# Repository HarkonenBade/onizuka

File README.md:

# onizuka
An FTDI based programming master board. With various daughter boards for programming specific modules.

## Current Daughter Boards
* ESP8266 (ESP-01, ESP-02, ESP-12E)

## License
Onizuka is licensed under [Creative Commons Attribution-ShareAlike 4.0 International (CC BY-SA 4.0)](http://creativecommons.org/licenses/by-sa/4.0/).

Psyduck (used in image on the ESP8266 board, due to the pun on ESP->ESP->Psychic) is Trademark & © of Nintendo 1996-2015

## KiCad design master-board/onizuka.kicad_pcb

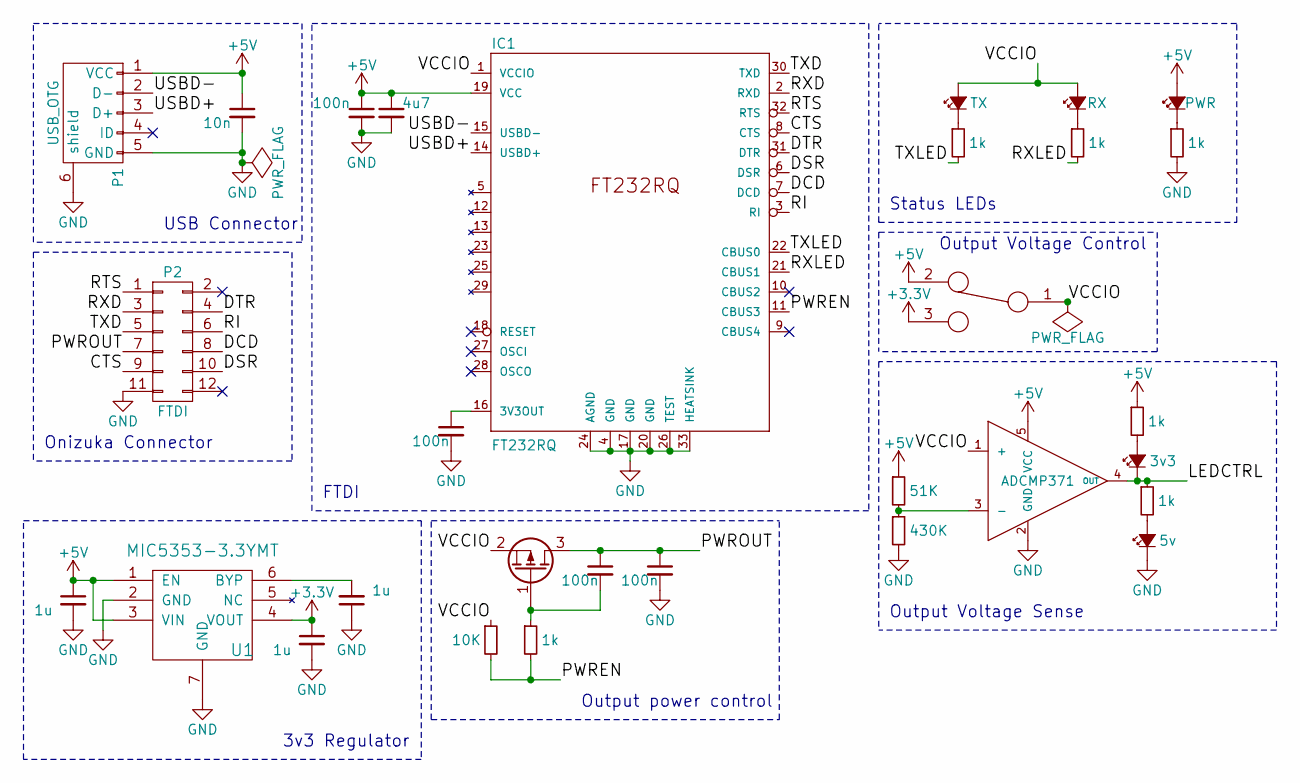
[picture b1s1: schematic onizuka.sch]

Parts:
C1, C4, C5, C6: 100n; C_0402; Farnell 2524677
C2: 10n; C_0402; Farnell 2524674
C3: 4u7; C_0402; Farnell 2426952
C7, C8, C9: 1u; C_0402; Farnell 2496813
D1: TX; LED_0603; Farnell 2290329
D2: RX; LED_0603; Farnell 8554609
D3: PWR; LED_0603; Farnell 8554609
D4: 3v3; LED_0603; Farnell 2290330
D5: 5v; LED_0603; Farnell 2290329
IC1: FT232RQ; FTDI-FT232RQ-QFN-32; Farnell 1146033
IC2: ADCMP371; SC-70-5; Farnell 2376801
P1: USB_OTG; USB_Micro-B; Farnell 2506104
P2: FTDI; Socket_Strip_Angled_2x06; Farnell 1668355
Q1: Q_PMOS_GSD; SOT-23; Farnell 1894738
R1, R2, R3, R4, R7, R8: 1k; R_0402; Farnell 1358043
R5: 51K; R_0402; Farnell 1358088
R6: 430K; R_0402; Farnell 1358113
R9: 10K; R_0402; Farnell 1358069
SW1: SPDT; 450301014042; Farnell 2134452
U1: MIC5353-3.3YMT; Thin_MLF_6_1.6mm_0.5mm_pitch; Farnell 2510347

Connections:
+3V3: C8.1, SW1.3, U1.4 (VOUT)
+5V: C2.1, C3.1, C4.1, C7.1, D3.2 (A), IC1.19 (VCC), IC2.5 (VCC), P1.1 (VCC), R5.1, R7.1, SW1.2, U1.1 (EN), U1.3 (VIN)
/CTS: IC1.8 (CTS), P2.9
/DCD: IC1.7 (DCD), P2.8
/DSR: IC1.6 (DSR), P2.10
/DTR: IC1.31 (DTR), P2.4
/LEDCTRL: D4.1 (K), IC2.4 (OUT), R8.1
/PWREN: IC1.11 (CBUS3), R4.2, R9.2
/PWROUT: C5.1, C6.1, P2.7, Q1.3 (D)
/RI: IC1.3 (RI), P2.6
/RTS: IC1.32 (RTS), P2.1
/RXD: IC1.2 (RXD), P2.3
/RXLED: IC1.21 (CBUS1), R2.2
/TXD: IC1.30 (TXD), P2.5
/TXLED: IC1.22 (CBUS0), R1.2
/USBD+: IC1.14 (USBD+), P1.3 (D+)
/USBD-: IC1.15 (USBD-), P1.2 (D-)
/VCCIO: D1.2 (A), D2.2 (A), IC1.1 (VCCIO), IC2.1 (+), Q1.2 (S), R9.1, SW1.1
GND: C1.2, C2.2, C3.2, C4.2, C6.2, C7.2, C8.2, C9.1, D5.1 (K), IC1.4 (GND), IC1.17 (GND), IC1.20 (GND), IC1.24 (AGND), IC1.26 (TEST), IC1.33 (HEATSINK), IC2.2 (GND), P1.5 (GND), P1.6 (shield), P2.11, R3.2, R6.2, U1.2 (GND), U1.7 (GND)
unnamed: C1.1, IC1.16 (3V3OUT)
unnamed: C5.2, Q1.1 (G), R4.1
unnamed: C9.2, U1.6 (BYP)
unnamed: D1.1 (K), R1.1
unnamed: D2.1 (K), R2.1
unnamed: D3.1 (K), R3.1
unnamed: D4.2 (A), R7.2
unnamed: D5.2 (A), R8.2
unnamed: IC2.3 (-), R5.2, R6.1

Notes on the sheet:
USB Connector
FTDI
3v3 Regulator
Output power control
Output Voltage Control
Onizuka Connector
Status LEDs
Output Voltage Sense

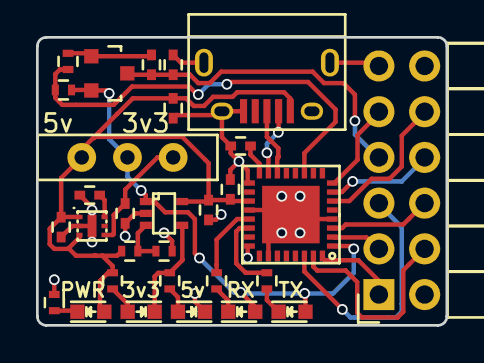
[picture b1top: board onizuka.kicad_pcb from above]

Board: 2 copper layers, 22.8 x 16.0 mm, 30 parts (0 on the bottom side), 28 nets.

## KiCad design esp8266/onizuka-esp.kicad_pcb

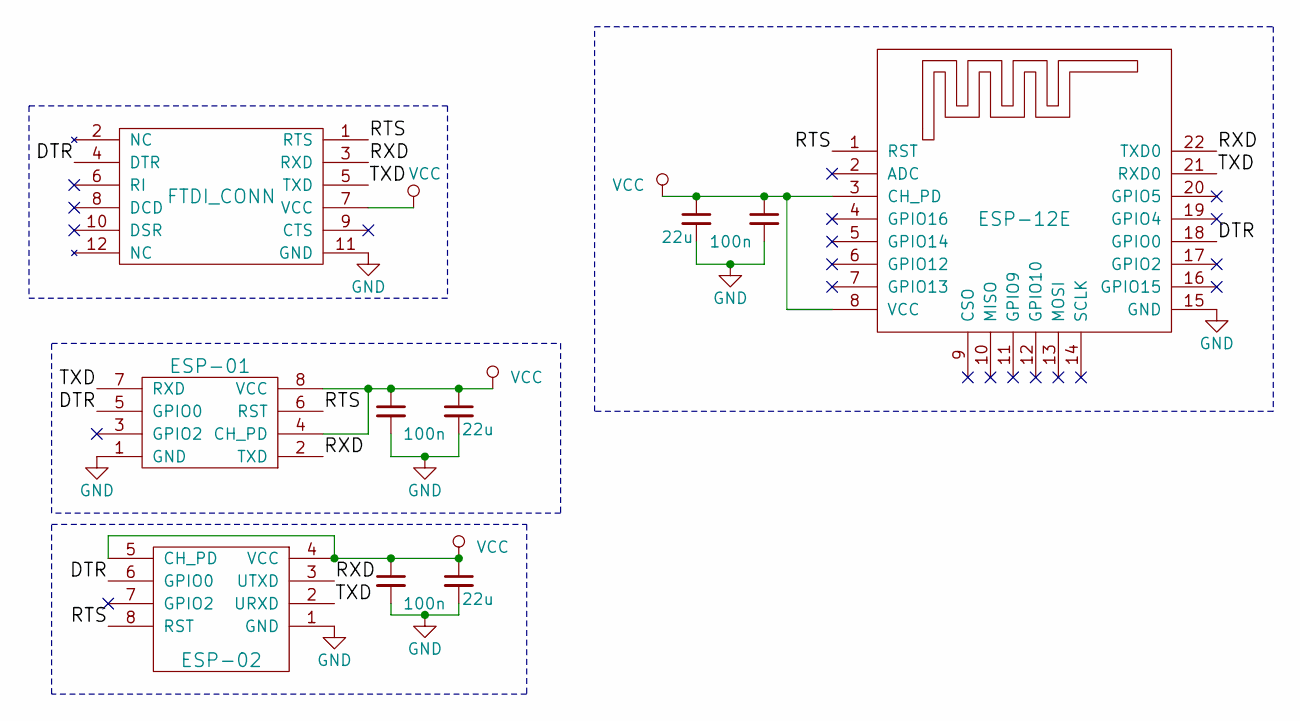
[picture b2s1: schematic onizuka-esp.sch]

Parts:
C1, C4, C6: 100n; C_0603; Farnell 2524817
C2, C3, C7: 22u; C_0603; Farnell 2494232
P1: FTDI_CONN; Pin_Header_Angled_2x06; Farnell 1593452
U1: ESP-01; Farnell 1593489
U2: ESP-12E; ESP-12E-Program
U3: ESP-02; ESP-02-Program

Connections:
/DTR: P1.4 (DTR), U1.5 (GPIO0), U2.18 (GPIO0), U3.6 (GPIO0)
/RTS: P1.1 (RTS), U1.6 (RST), U2.1 (RST), U3.8 (RST)
/RXD: P1.3 (RXD), U1.2 (TXD), U2.22 (TXD0), U3.3 (UTXD)
/TXD: P1.5 (TXD), U1.7 (RXD), U2.21 (RXD0), U3.2 (URXD)
GND: C1.2, C2.2, C3.2, C4.2, C6.2, C7.2, P1.11 (GND), U1.1 (GND), U2.15 (GND), U3.1 (GND)
VCC: C1.1, C2.1, C3.1, C4.1, C6.1, C7.1, P1.7 (VCC), U1.4 (CH_PD), U1.8 (VCC), U2.3 (CH_PD), U2.8 (VCC), U3.4 (VCC), U3.5 (CH_PD)

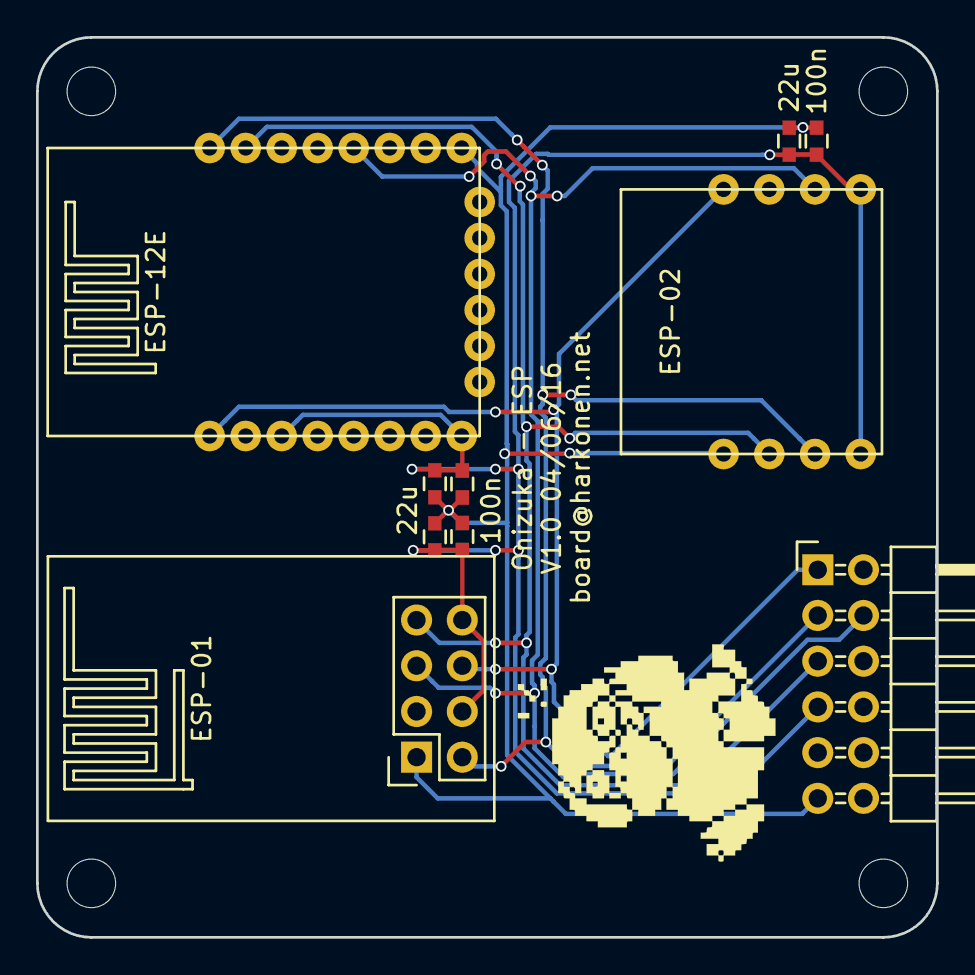
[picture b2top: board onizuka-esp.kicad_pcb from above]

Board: 2 copper layers, 50.0 x 50.0 mm, 10 parts (0 on the bottom side), 6 nets.

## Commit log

2016-05-20 INIT
2016-05-21 more shenanigans
2016-05-21 Filename correction
2016-05-23 ESP8266 daughter board
2016-05-23 Delete AMPHENOL FCI 10103592-0001LF.kicad_mod
    Fix bugged filename.
2016-05-24 Slight schematic rework, much PCB faffing
2016-05-25 Various upgrades, also ESP-12E footprint for ESP board
2016-05-30 More faffing
2016-05-31 Board reshuffle, new regulator
2016-05-31 3d model path correction
2016-05-31 Faffing, added connections to heatsink pad on FTDI, moved connector in slightly.
2016-05-31 Updated gitignore
2016-05-31 Tidied up schema, started to add farnell codes for components.
2016-06-01 Shift to independant kicad lib repo
2016-06-01 Various tweaks
2016-06-01 Keepup
2016-06-01 Add board names revisions and emails.
2016-06-01 Updated switch
2016-06-01 Poked around, fixed minor bug, tweaked silk slightly.
2016-06-02 Many faffing, new ESP stuff.
2016-06-03 Various shuffling, adding farnell part numbers.
2016-06-03 Centre pin header
2016-06-03 Rounded PCB corners
2016-06-03 ESP board rearrainge, also logo.
2016-06-04 Final tweaks, more farnell part numbers, BOM, gerbers
2016-06-04 Updated Thin MLF footprint, regenned gerbers
